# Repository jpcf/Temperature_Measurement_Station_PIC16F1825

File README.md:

## Temperature Measurement Station

Electronic Systems class Final Project. Consists of a Temperature/HeartRate monitor based on the PIC16F1825 uController. It uses a Nokia5110 LCD matrix as a means to display.

On the `include` folder, you can find a library that interfaces the display (`lib_LCD_Nokia5110`) and another for the 1-Wire Temperature Sensor (`ds18b20`). We also included a library that performs memory tests on all three memory types: RAM, ROM and EEPROM (` lib_memtest_PIC16F1825`).

You are free to use this code in your projects, but **please refer the authors**, *José Fonseca* (me) and *Carlos Ferreira*, from the **University of Porto, Portugal**.

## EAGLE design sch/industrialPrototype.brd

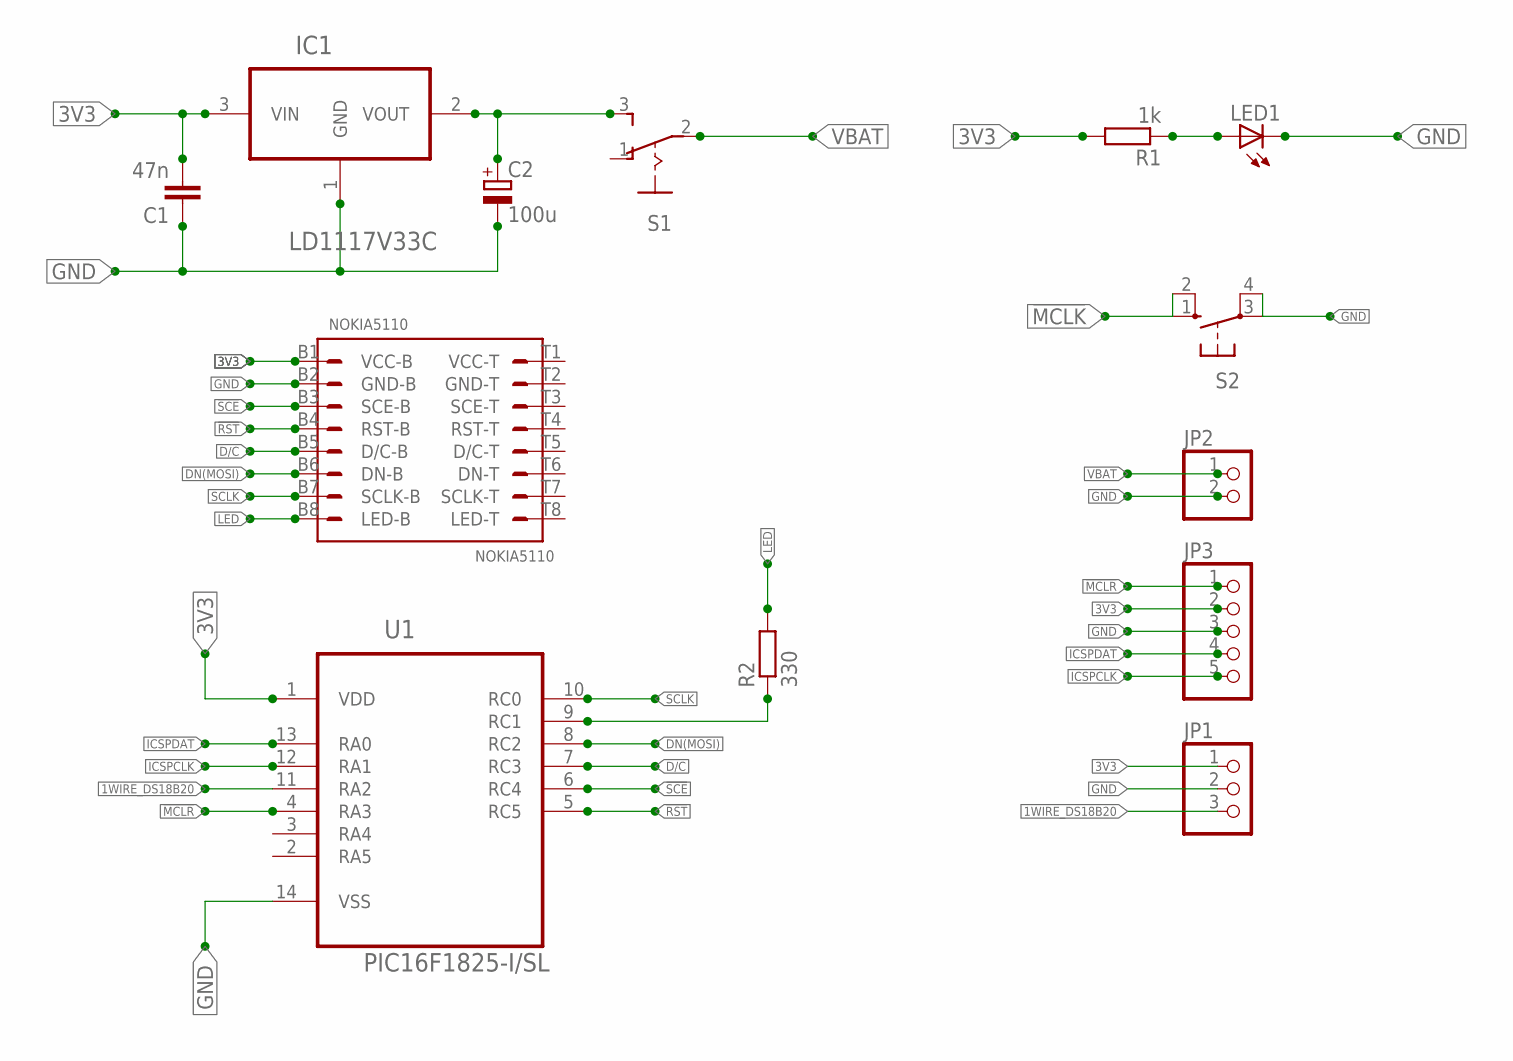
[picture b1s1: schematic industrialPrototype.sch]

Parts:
C1: 47n; C025-025X050
C2: 100u; E2,5-6
IC1: LD1117V33C; TO254P482X1024X3124-3P
JP1: PINHD-1X3; 1X03
JP2: PINHD-1X2; 1X02
JP3: PINHD-1X5; 1X05
LED1: LED3MM
NOKIA5110: NOKIA5110
R1: 1k; 0204/5
R2: 330; 0204/5
S1: 255SB
S2: 10-XX; B3F-10XX
U1: PIC16F1825-I/SL; SOIC127P600X175-14N

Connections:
1WIRE_DS18B20: JP1.3, U1.11 (RA2)
3V3: C1.2, IC1.3 (VIN), JP1.1, JP3.2, NOKIA5110.B1 (VCC-B), R1.2, U1.1 (VDD)
!MCLK!: S2.1 (S), S2.2 (S1)
!MCLR!: JP3.1, U1.4 (RA3)
!RST!: NOKIA5110.B4 (RST-B), U1.5 (RC5)
!SCE!: NOKIA5110.B3 (SCE-B), U1.6 (RC4)
D/C: NOKIA5110.B5 (D/C-B), U1.7 (RC3)
DN(MOSI): NOKIA5110.B6 (DN-B), U1.8 (RC2)
GND: C1.1, C2.-, IC1.1 (GND), JP1.2, JP2.2, JP3.3, LED1.K (C), NOKIA5110.B2 (GND-B), S2.3, S2.4 (P1), U1.14 (VSS)
ICSPCLK: JP3.5, U1.12 (RA1)
ICSPDAT: JP3.4, U1.13 (RA0)
LED: NOKIA5110.B8 (LED-B), R2.2
unnamed: LED1.A, R1.1
unnamed: R2.1, U1.9 (RC1)
SCLK: NOKIA5110.B7 (SCLK-B), U1.10 (RC0)
VBAT: C2.+, IC1.2 (VOUT), JP2.1, S1.2, S1.3 (S)

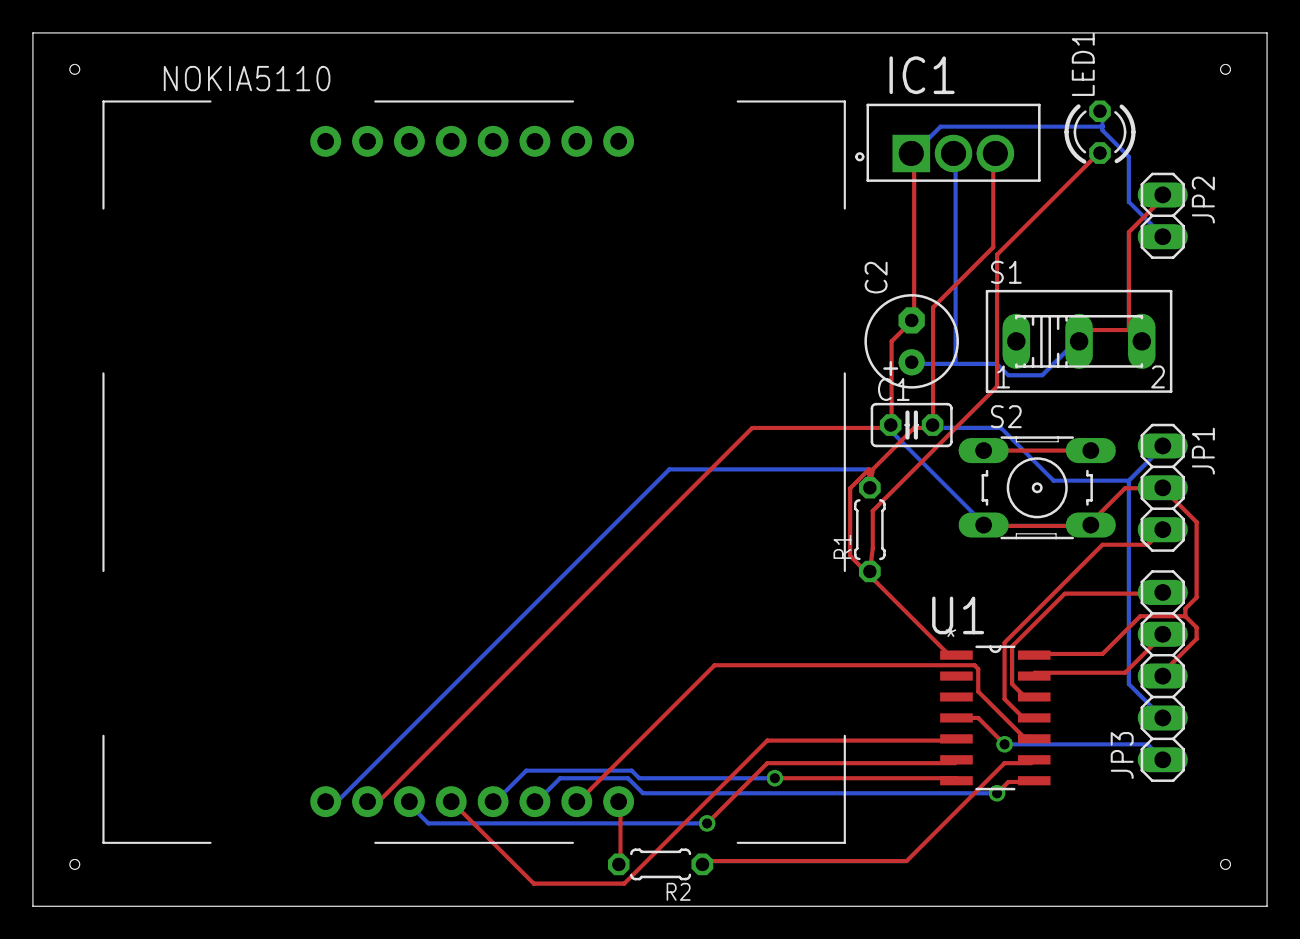
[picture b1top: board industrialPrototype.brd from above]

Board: 2 copper layers, 74.9 x 53.0 mm, 13 parts (0 on the bottom side), 16 nets.

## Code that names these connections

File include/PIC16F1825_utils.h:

/*
Authors: José Pedro Fonseca, Carlos Ferreira, 2015
University of Porto, Portugal
*/


#ifndef _PIC16F1825_UTILS_
#define _PIC16F1825_UTILS_

#include <xc.h>
#include <stdint.h>


/* PINS */
#define RA2 0x04

#define RC0 0x01
#define RC1 0x02
#define RC2 0x04
#define RC3 0x08
#define RC4 0x10
#define RC5 0x20


void pic16f1825_init(void); /* Configure PIC16F1825 oscillator */


/* MAKE SURE THAT THE INTERRUPTS ARE DISABLED BEFORE USING THE 1-WIRE FUNCTIONS TO AVOID TIMING PROBLEMS */
/* The following functions assume that the RA2 pin is used */

bit one_wire_init(); /* init sequence for 1-wire protocol */
void one_wire_write_bit(uint8_t bit_value);
void one_wire_write_byte(uint8_t byte_value);
bit one_wire_read_bit();
uint8_t one_wire_read_byte();

/* Functions to access EEPROM */
void write_eeprom(uint8_t addr, uint8_t data);
uint8_t read_eeprom(uint8_t addr);

#endif

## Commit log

2015-11-24 Delete README.md
    This needs to go before I sync with the local folder
2015-11-24 First Commit: The first prototype for the README.md file
2015-11-24 The test file for the LCD driver
2015-11-25 Added the datasheets for the relevant components of the system
2015-11-25 Code partially works on physical LCD. Still, the configurations need to be tinkered through
2015-11-25 Now the LCD completely works, and is able to print data. Need to clean the file, separate the functions to another file, and find a suitable font
2015-11-26 Found out that MPLABX accepts any name for its main file. Changed the name, and deleted the folder
2015-11-26 Created a separate header file for the LCD Libraries
2015-11-26 Added font support to the Library, and a function to print a char that partially works
2015-11-28 The working main file to test the Nokia5110 graphical library
2015-11-28 Copied the configuration code for a separate function. Also, Added a function that clears the LCD
2015-11-28 Alphabet seems to work. Changed array to .c file. Need to find a definite soluton
2015-11-28 Changed the testSPI.c file. Now prints the whole alphabet, but somehow starts filling blanks afterwards
2015-11-28 Error corrected. Added padding to the right of each caracter
2015-11-28 Added function that sends several bytes at a time
2015-11-28 Added support to print lines, and go to a specified address. There are still some issues
2015-11-28 Now tests several lines
2015-11-28 The positioning now seems to work completely. Just need to figure out a problem with the string pointers!
2015-11-29 Added further printlnLCD function, and also corrected the pointer issue of the send_N_ByteLCD()
2015-11-29 Now makes use of the printlnLCD, and uses sprintf to format the string
2015-11-29 This script dithers any image, and outputs a file suitable for input to the Nokia5110
2015-11-29 Now prints in hex format correctly
2015-12-01 Added the RAM testing library. Still doesn't work
2015-12-01 Added a functional graphics display library
2015-12-02 Further developed the memory tests. Still doesn't write past 0x23EF
2015-12-02 Updated the test files
2015-12-02 Missing declaration in the .h file
2015-12-02 Changed the Font Array to const type. This way, it goes to program memory instead of Data Memory
2015-12-02 Now the RAM testing library fully works
2015-12-02 The example usage main file for the memory testing library
2015-12-02 Foram adicionados varios ficheiros. pic16f1825_configs .h e respectivo .c pic16f1825_utils.h e respectivo .c ds18b20.h e respectivo .c
    Foi alterado o lib_memtest_pic16f1825.c e respectivo .h em que se adicionou a função que testa a ROM
    Foi também adicionado o ficheiro /src/main.c que contem a funcao main
2015-12-02 ao ao pino usado no 1-wire que agora é o RA2 FOi retirado o _RC2_ dos nomes das funcões 1-wire
2015-12-02 The first sketch of the final executable. Only missing the integration with OneWire readings
2015-12-02 Added a few changes to allow integration with other libs
2015-12-02 Cleaned the file
2015-12-03 Improved the main file and the graphics library. Still missing the sensor integration
2015-12-03 Changes during the presentation
2015-12-03 Corrigido bug do teste da ROM
2015-12-13 Foi adicionado o teste da EEPROM Foram adicionadas as funcoes eeprom_read e eeprom_write Foi adaptado o main para utilizar as novas funçoes
2015-12-15 Added the schematic. Still missing connections to temp sensor and other
2015-12-15 Schematic almost finished. Only temp sensor header missing
2015-12-15 Added Programming Header. Placed components on PCB. Routing still has to be done
2015-12-16 Added the screen and did the auto-route. Labels still need to be fixed
2015-12-18 Added the Temperature Sensor Socket
2015-12-20 Cleaned up
2015-12-23 MISRA
2015-12-23 Final Version of the Schematic and Board
2016-01-02 Final version
